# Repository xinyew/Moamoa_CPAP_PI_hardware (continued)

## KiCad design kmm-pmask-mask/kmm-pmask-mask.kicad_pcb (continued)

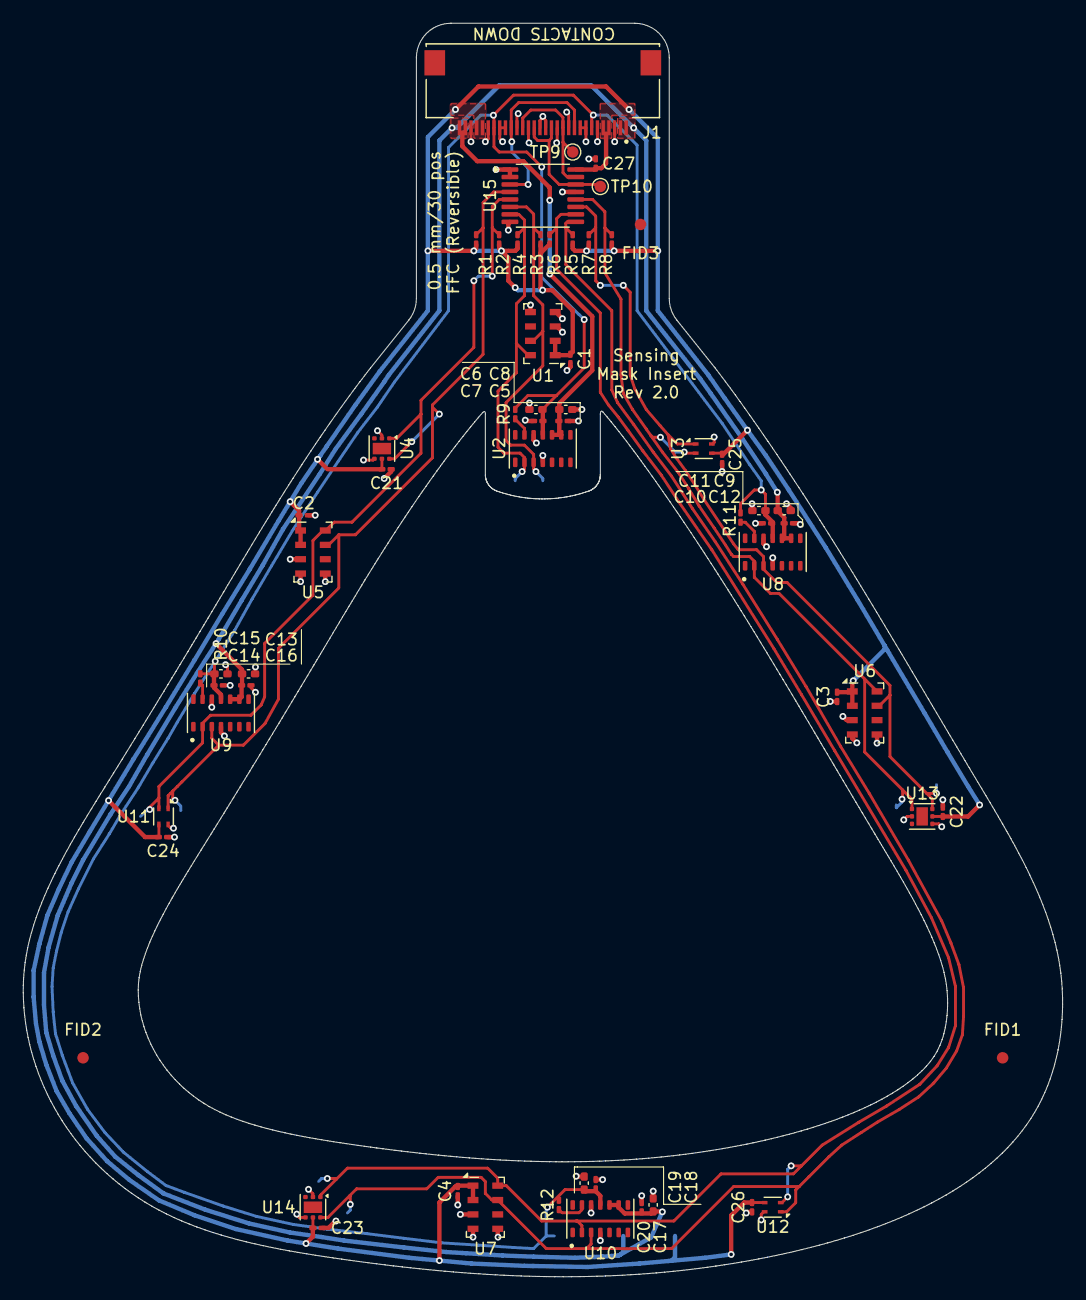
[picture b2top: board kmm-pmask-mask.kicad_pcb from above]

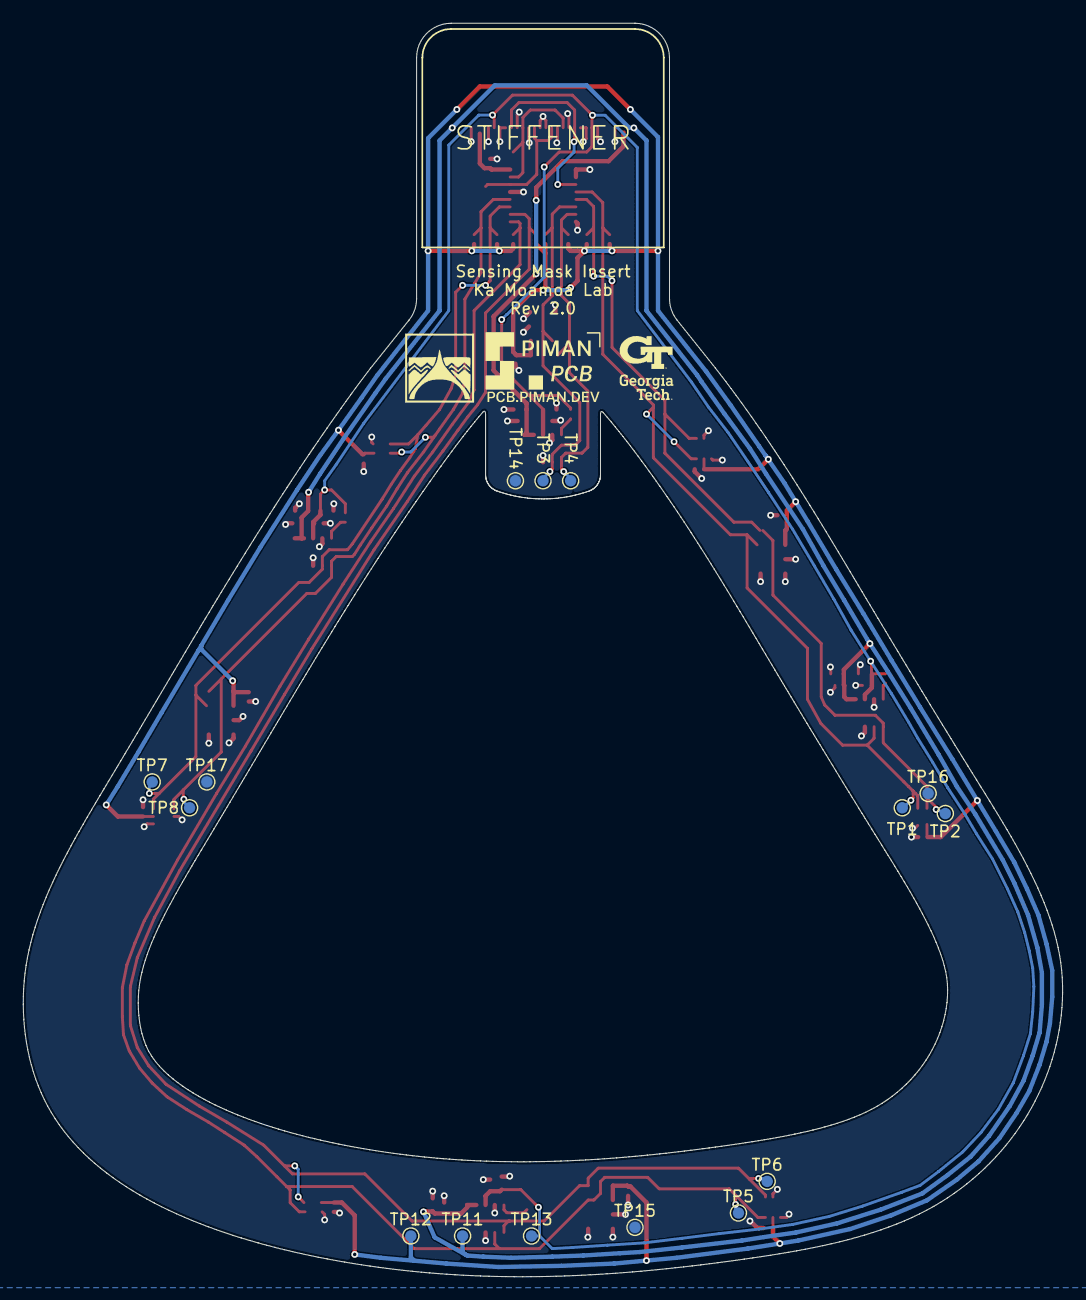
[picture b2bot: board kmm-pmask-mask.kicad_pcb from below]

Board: 2 copper layers, 90.4 x 109.0 mm, 75 parts (15 on the bottom side), 19 nets.
